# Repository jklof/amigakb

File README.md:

# amigakb
Arduino Amiga keyboard interface

This is a bit of code that allows you to use Amiga hw keyboard as USB HID keyboard.
Useful for projects such as replacing Amiga internals with Raspberry.

---

This is a fork of jklof/amigakb adjusted for Vampire V4-SA

This should work with all Amiga keyboards that have their own controller (i.e. all keyboards except A600 and A1200):
- A500
- A1000 (early and later models)
- A2000/A3000
- A4000/CD32
- CDTV

The repository also contains [schematics and premade board files](boards) for building a "Pro Micro" based adapter that runs this code.
3D printable cases for the boards can be found at https://www.thingiverse.com/thing:4593520

### Changes to the original code:
- Merged in changes from https://forum.arduino.cc/index.php?topic=139358.90
- Changed Backslash, Hash and Help key mappings
- Added reset handling for keyboards without reset line
- Made use of the caps lock special handling (for compensating differences between Amiga and USB keyboard protocols)
  configurable via a jumper (V4 expects key events differently than usual for USB keyboards)
  This can be switched with a jumper between pin 2 and ground.
- replaced digitalRead() with direct register usage to meet timing requirements for early A1000 keyboards
- changed handshake to work with early A1000 keyboards
- send data via USB during handshake pulse, in order to not miss next key event
- Added option to use a switch between pin 4 and ground to select an alternative keymap in order to make codes of keys available that do not exist on the amiga keyboard (currently only used for providing F11 and F12 (which are used by V4SA to toggle options) on F1 and F2)

### Uploading the precompiled hex file to the microcontroller
To ease the installation process I've uploaded a precompiled build: [amigakb.hex](amigakb.hex)
This file can be uploaded to the microcontroller using AVRDUDE: https://www.nongnu.org/avrdude/

#### Linux

Most distributions likely have an AVRDUDE package, for example on Ubuntu it can be installed using:
```
sudo apt-get install avrdude
```
When you plug in a "fresh" pro-micro the built-in CDC serial port will be recognized as a tty.
Here is an example output of `dmesg` when the microcontroller gets connected:
```
usb 1-9: new full-speed USB device number 110 using xhci_hcd
usb 1-9: New USB device found, idVendor=2341, idProduct=0036, bcdDevice= 0.01
usb 1-9: New USB device strings: Mfr=2, Product=1, SerialNumber=0
usb 1-9: Product: Arduino Leonardo
usb 1-9: Manufacturer: Arduino LLC
cdc_acm 1-9:1.0: ttyACM0: USB ACM device
```
Here the name of the serial port is `ttyACM0`.
This port can be used to program the microcontroller with the downloaded hex file:
```
sudo avrdude -v -patmega32u4 -cavr109 -P/dev/ttyACM0 -b57600 -D -Uflash:w:amigakb.hex:i
```
#### Windows

You can download a Windows version of AVRDUDE from https://github.com/mariusgreuel/avrdude/releases.

Extract the AVRDUDE package and place the [amigakb.hex](amigakb.hex) file right next to the extracted files. Start a Windows Command Prompt in the same directory (for example by typing `cmd.exe` in the explorer address bar).

When you plug in a "fresh" pro-micro the built in CDC serial port will be recognized as a new COM port.

In this example the device manager has an entry called `USB Serial Device (COM5)`.

This port can be used to program the microcontroller with the downloaded hex file.
In the Windows Command Prompt type:
```
avrdude.exe -v -patmega32u4 -cavr109 -v -PCOM5 -b57600 -D -Uflash:w:amigakb.hex:i
```

### Building for V4-SA:
- Use Arduino IDE v1.6.5-r5 (needed for the changes below - the last version before a refactoring of the USB stack).
  Note that if you have used a newer version, such as 1.8.x, it might prevent the 1.6.5 version from working due to it using
  incompatible compiler switches or adding incompatible packages.  If you get a linker error mentioning LTO (Link Time Optimisation)
  it will certainly be caused by this.  To resolve the issue, on Windows, search in your c:\Users\<UserName>\AppData directory
  for a directory called "Arduino15" and delete it.  There will probably be one in AppData\Local and one in AppData\Roaming.
  You might have to repeat this process to switch back to the newer Arduino IDE version.  On MacOS the directory can be found in
  ~/Library/Arduino15 and on Linux it is in ~/.arduino15.
- When installing the Pro Micro board add-on for Arduino IDE, do *not* use the automated installation method or it will recreate
  the Arduino15 directory and result in a non working build (as it installs the add-on for the latest 1.8.x version of the Arduino
  IDE).  Instead, download and install the board add-on manually, as described on the Sparkfun website at
  https://learn.sparkfun.com/tutorials/pro-micro--fio-v3-hookup-guide/installing-windows under the section entitled "Installing the
  .brd Files Manually".  This is an older version of the add-on designed for older versions of the Arduino IDE
- Apply the change from https://github.com/tkoecker/Arduino/commit/e6783cb5e4b7e1dc8abc4932b3e3543ad793c6ff.patch to
  get an USB core that uses low-speed USB, with only one boot protocol keyboard HID device.  Experience has shown that some versions
  of patch do not work properly (at least on Windows), so look out for error messages such as "Hunk #X FAILED at XXX." or you'll
  be building an unpatched USB stack and will wonder why it doesn't work on the Vampire!

### TODO:
- Add reset handling for A500 keyboard (i.e. keyboard with reset line) (optional as the current reset handling also is sufficient for A500 keyboards)
- Fix mapping of numpad '(' and ')' keys (Amiga keycodes 0x5a, and 0x5b) (these seem currently not to be available on V4)
- A500 keyboard: make LEDs controllable via USB (i.e. switch drive led on/off, switch power led bright/dim)

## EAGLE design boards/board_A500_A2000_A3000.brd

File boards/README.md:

This directory contains boards (as EAGLE CAD files) that can be used in combination with the [code in this repository](..).

They allow to create a DIY adapter which requires three things:
* A "Pro Micro" Arduino clone (5 Volt version)

* One of the adaptor boards fitting to the keyboard you want to use (the A500 pin header can be used on any of the boards)
  * A1000 ([pcbway link](https://www.pcbway.com/project/shareproject/Amiga_1000___500_Keyboard_USB_adapter.html))
  * A2000 / A3000 ([pcbway link](https://www.pcbway.com/project/shareproject/Amiga_2000___3000___500_Keyboard_USB_adapter.html))
  * A4000 / CD32 ([pcbway link](https://www.pcbway.com/project/shareproject/Amiga_4000___CD32___500_Keyboard_USB_adapter.html))
  * CDTV ([pcbway link](https://www.pcbway.com/project/shareproject/Amiga_CDTV___500_Keyboard_USB_adapter.html))

* The corresponding socket to attach the keyboard to:
  * A1000: 4P4C socket
  * A2000 / A3000: 5 pin DIN socket
  * A4000 / CD32: 6 pin mini-DIN socket
  * CDTV: 5 pin mini-DIN socket
  * A500: 8 pin standard 2.54 mm (0.1 in) pin header

To build one of these just solder the "Pro Micro" board and the socket or pin header on the adaptor board, create a solder bridge on J1 of the "Pro Micro", and flash the [software](..).

3D printable cases for the boards can be found at https://www.thingiverse.com/thing:4593520

***DISCLAIMER:***

This hardware/software is provided "as is", and you use the hardware/software at your own risk. Under no circumstances shall any author be liable for direct, indirect, special, incidental, or consequential damages resulting from the use, misuse, or inability to use this hardware/software, even if the authors have been advised of the possibility of such damages.

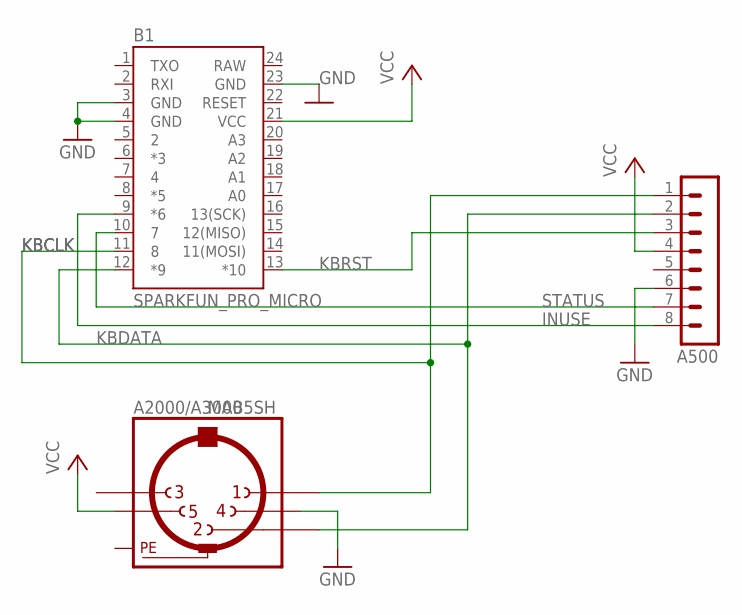
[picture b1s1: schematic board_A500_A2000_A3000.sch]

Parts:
A500: MA08-1
A2000/A3000: MAB5SH
B1: SPARKFUN_PRO_MICRO

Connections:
GND: A500.6, A2000/A3000.4, B1.3 (GND), B1.4 (GND), B1.23 (GND)
INUSE: A500.8, B1.9 (*6)
KBCLK: A500.1, A2000/A3000.1, B1.11 (8)
KBDATA: A500.2, A2000/A3000.2, B1.12 (*9)
KBRST: A500.3, B1.13 (*10)
PE: A2000/A3000.PE, A2000/A3000.PE@ (PE)
RAW: B1.24 (RAW)
STATUS: A500.7, B1.10 (7)
VCC: A500.4, A2000/A3000.5, B1.21 (VCC)

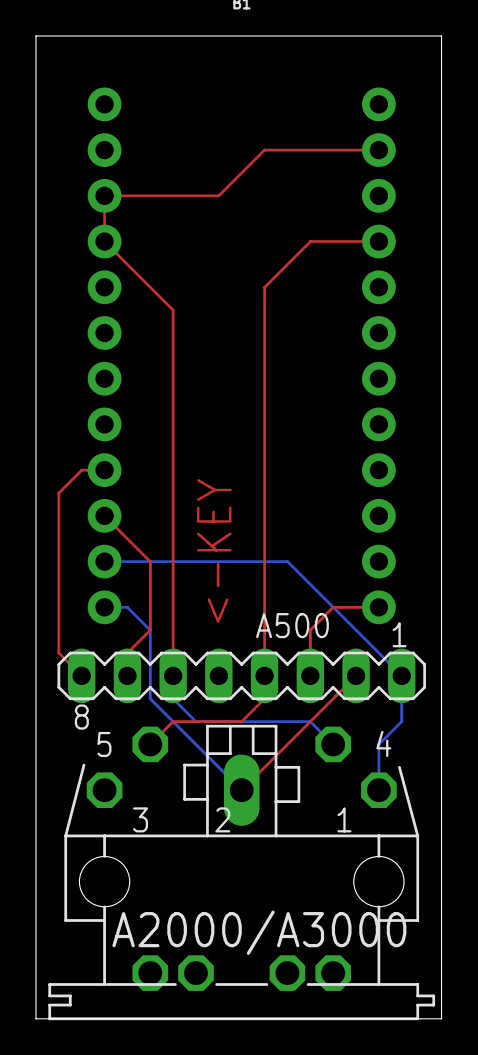
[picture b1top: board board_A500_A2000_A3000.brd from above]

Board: 2 copper layers, 22.5 x 54.6 mm, 3 parts (0 on the bottom side), 8 nets.

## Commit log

2016-05-06 Amiga 500 keyboard interface for Arduino
    - You can control power/disk drive leds
    - Read raw key codes
    - TODO: make arduino work as USB HID
2016-05-06 C++ify
    - wrap it to C++ class
2016-05-26 Emulate USB keyboard
    - rudimentary HID device support
    to emulate USB keyboard
2016-05-28 Added keypad code mappings
2016-05-28 code cleanup
2020-02-02 applied changes from https://forum.arduino.cc/index.php?topic=139358.90
2020-02-02 fix some keycodes, add reset handling for keyboards without reset line, disable caps lock special handling for vampire
2020-02-03 warning fix, check for arduino ide version
2020-02-05 make use of caps lock special handling configurable via a jumper
2020-02-07 added boards
2020-02-07 fix socket orientation
2020-02-07 added comment that 5V version of pro micro is needed
2020-02-12 hole placement fixes
2020-02-19 fix support for early A1000 keyboards (improve read speed), fix handshake, do USB stuff during handshake pulse
2020-03-01 added pcbway links
2020-03-08 added option to use a switch to select an alternative keymap, making F11 and F12 keycodes available
2020-09-10 added 3d printable cases
2021-10-07 Improve instructions on how to compile using Arduino IDE 1.6.5
    Switching back to the old IDE is quite difficult for newcomers who
    are not familiar with it. These extra instructions should help
    to avoid at least some of the worst pitfalls.
2021-10-07 Update README.md
    Added linux path
2023-01-16 added precompiled .hex file and description how to upload it
2023-01-17 Updated link to windows AVRDUDE to a version that handles the bootloader reset

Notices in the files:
parts and their libraries:
SparkFun-Boards: Licensing: Creative Commons ShareAlike 4.0 International - https://creativecommons.org/licenses/by-sa/4.0
